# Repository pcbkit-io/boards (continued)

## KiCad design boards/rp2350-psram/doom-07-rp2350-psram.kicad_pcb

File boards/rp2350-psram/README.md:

# 07 · rp2350-psram — the bare RP2350A with QSPI flash and PSRAM on one bus

The reference device's chip without the module: an RP2350A with Raspberry Pi's minimal design
(core switching regulator, 12 MHz crystal), a 16 MB W25Q128 on QSPI chip select 0 and an 8 MB
APS6404L PSRAM on the QMI's chip select 1 (GPIO8) sharing the same SCLK and SD0–SD3, so both are
memory-mapped through the XIP cache and Doom runs as an ordinary program. Two 18650 Li-ion cells
power it, behind reverse-cell and DW01A protection, charged from the USB-C by a BQ24075 with power
path, with a MAX17048 fuel gauge and a switched LDO. JLCPCB assembles everything but the display
module, which plugs into the socket it solders.

| | |
|---|---|
| Processor | RP2350A (QFN-60): 2 × **Cortex-M33** (ARMv8-M Mainline, FPU, DSP, TrustZone) **or** 2 × **Hazard3** RISC-V (RV32IMAC + Zba/Zbb/Zbs/Zbkb/Zcb/Zcmp), the architecture chosen by the image; 150 MHz; 520 KB SRAM; on-chip 1.1 V switching regulator (3.3 µH) |
| Memory | W25Q128JVSIQ 16 MB on QSPI_SS (CS0); APS6404L-3SQR 8 MB PSRAM on GPIO8 = QMI CS1 (XIP_CS1n); both mapped by the QMI (flash at 0x1000_0000, PSRAM at 0x1100_0000), 16 KB XIP cache |
| Display | 2.0" 240 × 320 IPS, ST7789 (MSP2008), SPI0 (GPIO18 SCK, GPIO19 MOSI, GPIO17 CS, GPIO16 DC, GPIO20 RES, GPIO21 backlight); landscape 320 × 240 |
| Storage | microSD on SPI1 (GPIO10–13), card detect GPIO14 |
| Input | 10 × 6 mm tact switches: GPIO0–5 (d-pad, fire, use), GPIO9, GPIO15 (strafe), GPIO25 (menu), GPIO26 (enter) |
| Sound | PIO I2S (GPIO22 BCK, GPIO23 LRCK, GPIO24 DIN) → MAX98357A → 8 Ω speaker |
| Power | 2 × 18650 Li-ion in parallel (1S2P) → reverse-cell P-FET (AO3401A) → DW01A + FS8205A; USB-C (1 A PTC + TVS) → **BQ24075** (power path SYS; USB500 mode, 800 mA charge) → TLV75533 (EN on the slide switch) → 3.3 V; **MAX17048** gauge on the pack, on I2C1 (GPIO6 SDA, GPIO7 SCL, 0x36, alert GPIO29); amplifier on SYS |
| Programming | USB-C to the RP2350's USB (27 Ω, USBLC6 ESD array): hold BOOT (1 kΩ on QSPI_SS), tap RESET → the boot ROM's UF2 drive, for ARM or RISC-V images; SWD + RUN on a 4-pin header on the back |
| Board | 144 × 110 mm, **4 layers** (In1 a solid GND plane), four M3 holes; front: display, buttons, BOOT, RESET, on/off switch, USB-C, charge LEDs, test pads; back: the RP2350 and the rest, the two 18650 holders across the top half. Net classes: 0.15 mm tracks and gaps with 0.45 / 0.2 mm vias by default (the QFN-60's 0.4 mm pitch), 0.3 mm for 3.3 V and the core, 0.6 mm with 0.8 / 0.4 mm vias for the power paths |

<!-- STATUS -->
**Board status** (measured on the dev host with PCBKit's CLI): `pcbkit check`: complete — 0 errors, 3 warnings (diff-pair-uncoupled, skew, track-width-class), 0 unrouted nets; `issues` has 3 of 3. 100 components, 75 nets, 1224 track segments (3267 mm), 166 vias.
`analysis.run { lens: "ready" }`: Typical scenario, partly by family estimates. Nothing to fix, 5 to consider, 14 ok: weigh the warnings (tell the person about the ones that are their choice), then the board is ready to order.
`pcbkit export --format fab` succeeds without `--force`: every assembled line of the BOM has an LCSC code.

| Warning | Why it stays |
|---|---|
| `diff-pair-uncoupled`, `skew` (DP / DN, ~60 mm) | USB full speed (12 Mbit/s): the connector is on the front edge, the RP2350 on the back; tens of mm uncoupled and ten of skew (~70 ps) are harmless against 4–20 ns edges |
| `track-width-class` (DP necked to 0.15 mm) | a short neck at the 0.4 mm pitch pads; a signal |
| ready lens: J3 is not on an edge | the SWD header is for a debug probe's jumper wires, not a cable to the outside |
| ready lens: thermal parameters, typical scenario | estimates of the analysis, not faults of the board |
<!-- /STATUS -->

## Run it in the browser

Open https://app.pcbkit.io/github/pcbkit-io/doom-handheld/tree/main/boards/rp2350-psram, open the
Laboratory and press **Run**: the page builds `doom/` for the RP2350 (with `DOOM1.WAD` linked into
flash), boots the image on a register-level model of the chip and its PSRAM, and draws the
display's frames on the board. Play with the keyboard (arrows, F fire, Space use, comma/period
strafe, M menu, Enter) or a gamepad (`input.js` maps a standard controller).

## Why it runs Doom

This is the reference device's software on its own board: Doom with its zone heap and screens in
the PSRAM, the shareware WAD linked into the flash, on one Hazard3 core at 150 MHz; each 320 × 200
frame goes to the display as RGB565 over SPI0 at 25 MHz. Not measured on hardware: the simulation
runs one instruction per clock and charges no flash or PSRAM latency.

## Power

Two 18650 Li-ion cells in Keystone 1042 holders on the back, in parallel (1S2P, 3.0–4.2 V, about
5–7 Ah together), as on `rp2350-handheld`:

- **Reverse cells:** an AO3401A P-MOSFET in the plus line, its gate at the cells' minus: cells put
  in backwards leave it off and the board unpowered (it conducts both ways when they are right, so
  charging goes through it too). It cannot help one cell reversed against the other: in parallel
  they would short each other, so check both against the silkscreen's + before closing a case.
- **Protection:** DW01A + FS8205A in the pack's minus: over-charge 4.3 V, over-discharge 2.4 V,
  over-current about 3 A and short circuit, for the pack. Flat-top unprotected 18650 cells fit
  the holders.
- **Charger with power path:** a TI BQ24075 (the BQ24074's sibling with SYSOFF and a fixed
  current-based termination) from the USB-C VBUS (through a 1 A PTC fuse, a 5 V TVS after it), in
  USB500 mode (at most 500 mA from the port; 5.1 kΩ on CC), 800 mA fast charge (RISET 1.13 kΩ),
  input limit RILIM 1.18 kΩ, safety timers off (two cells charge longer than its longest timer),
  TS tied to 10 kΩ (no thermistor). Its output SYS runs the board from USB when one is plugged in
  (flat or missing cells included) and from the cells otherwise.
- **Fuel gauge:** the MAX17048 measures the pack after the protection (its ModelGauge needs no
  sense resistor; two cells in parallel read as one cell of twice the capacity).
- **Rails:** SYS feeds the TLV75533 LDO (3.3 V; it follows the cells below about 3.55 V) and the
  MAX98357A directly; the slide switch on the left edge enables the LDO (100 kΩ holds it off), the
  amplifier is shut down by its SD_MODE while the RP2350 is off. The cells keep charging with the
  switch off.

| State | Current (estimate) |
|---|---|
| RP2350 at 150 MHz + PSRAM + flash | ~45 mA at 3.3 V |
| ST7789 2.0" with backlight | ~40 mA |
| MAX98357A | 20–200 mA from SYS |
| **Typical** | **~120 mA at 3.7 V** |

Two 3000 mAh cells → **about 50 h** of play (estimate). A full charge of two empty cells at 800 mA
takes about 8 h (longer from a 500 mA USB 2.0 port).

## Charging

Plug a USB-C charger or computer into the USB-C on the bottom edge. The red LED (CHG) is on while
the cells charge and goes out when they are full; the green LED (USB) is on while USB power is
present. The board runs from USB while it charges, switched on or off. Insert both cells with +
at the end the back's silkscreen marks.

## Flashing on arrival

Nothing to solder and no programmer: the RP2350's boot ROM has a USB loader.

1. Connect the USB-C to a computer.
2. Hold **BOOT**, tap **RESET**, release BOOT (or hold BOOT while plugging in): the board appears
   as the **RP2350** drive.
3. Copy `U1.uf2` onto it (the boot ROM runs Arm or RISC-V images); or
   `picotool load -x U1.uf2` with the board in BOOTSEL.

Or over SWD: the 4-pin header on the back (SWCLK, GND, SWDIO, RUN) takes a Raspberry Pi Debug
Probe. The game data goes in the flash with the program.

## Modules plugged in by hand

- **DS1: 2.0" 240 × 320 ST7789 IPS SPI module** (MSP2008 pinout, 8 pins: GND, VCC, SCL, SDA, RES,
  DC, CS, BLK) into the 1x8 socket JLCPCB solders on the front.
- An **8 Ω speaker** (up to 3 W) with a JST PH 2-pin plug into J5 at the right edge of the back.
- Two **18650 cells**.

## Firmware: build

- `doom/` is the program: `doom_rp2350.c` is the platform layer (clocks from the 12 MHz crystal,
  the PSRAM on QMI chip select 1 = GPIO8, which the firmware sets up — the boot ROM only sets up
  CS0 — the display, the buttons, the timer), the engine is sysprog21/doom_riscv, unchanged. Pins:
  display SCK GPIO18, MOSI GPIO19, CS GPIO17, D/C GPIO16, RESET GPIO20, backlight GPIO21; buttons
  up GPIO0, down 1, left 2, right 3, fire 4, use 5, strafe left 9, strafe right 15, menu 25,
  enter 26. The ST7789's IPS panel needs inversion on (INVON) for true colours. Not used yet: the
  microSD card, the amplifier, the fuel gauge; no console (GPIO0 and GPIO1 are buttons).
- **Build:** in PCBKit, the Laboratory's **Run** builds it (RISC-V, `DOOM1.WAD` linked into flash);
  then export the firmware (`export.run { format: "firmware" }`, or the app's export menu): `U1.uf2`.

## Bill of materials

Rough cost at 10 pieces (estimates): RP2350A $1.10 · W25Q128 $1.00 · APS6404L $1.20 · crystal $0.15 ·
3.3 µH inductor $0.20 · ST7789 2.0" $4.00 · microSD socket $0.60 · MAX98357A $0.90 · BQ24075 $1.10 ·
DW01A + FS8205A + AO3401A $0.25 · MAX17048 $1.60 · TLV75533 $0.20 · USB-C + ESD + TVS + PTC $0.50 ·
buttons $3.50 · passives $2.00 · two 18650 holders $9.80 · 4-layer PCB $4.00 · speaker $1.00 →
**about $37** without the cells, plus assembly.

<!-- BOM -->
The assembly BOM as `pcbkit export --format fab` writes it (JLCPCB assembly: LCSC codes; the modules' lines are their sockets):

| Qty | Refs | Part | LCSC | Footprint |
|---|---|---|---|---|
| 2 | BT1, BT2 | 1042 | C5249310 | BatteryHolder_Keystone_1042_1x18650 |
| 1 | C1 | 10uF | C19702 | C_0603_1608Metric |
| 2 | C2, C3 | 15pF | C1548 | C_0402_1005Metric |
| 16 | C4, C5, C6, C7, C8, C9, C10, C11, C12, C13, C14, C18, C19, C21, C23, C27 | 100nF | C1525 | C_0402_1005Metric |
| 5 | C15, C16, C17, cBat, cSys | 4.7uF | C1779 | C_0805_2012Metric |
| 1 | C20 | 1uF | C52923 | C_0402_1005Metric |
| 1 | C22 | 10uF | C15850 | C_0805_2012Metric |
| 3 | C28, C29, cIn | 1uF | C15849 | C_0603_1608Metric |
| 1 | D1 | tvs 5V | C918844 | D_SOD-323 |
| 1 | DS1 | Female header 1x8 2.54 mm | C2905417 | TFT_2.0in_ST7789_Socket_1x08_P2.54mm |
| 1 | F1 | PTC 1000mA | C20800 | Fuse_1206_3216Metric |
| 1 | J1 | USB_C_Receptacle_USB2.0_16P | C165948 | USB_C_Receptacle_USB2.0_16P |
| 1 | J3 | PinHeader_1x04_P2.54mm_Vertical | C2691448 | PinHeader_1x04_P2.54mm_Vertical |
| 1 | J4 | DM3AT-SF-PEJM5 | C114218 | Hirose_DM3AT_microSD_socket_push-push |
| 1 | J5 | S2B-PH-K-S(LF)(SN) | C173752 | JST_PH_S2B-PH-K_1x02_P2.00mm_Horizontal |
| 1 | L1 | 3.3uH | C83456 | L_Power_6x6mm |
| 1 | Q1 | AO3401A | C15127 | SOT-23 |
| 1 | Q2 | FS8205A | C5148694 | TSSOP-8_4.4x2.93mm_P0.65mm |
| 7 | R1, R2, R3, R4, R5, R12, rTs | 10kohm | C25744 | R_0402_1005Metric |
| 2 | R6, R16 | 100kohm | C25741 | R_0402_1005Metric |
| 3 | R7, R11, R18 | 1kohm | C11702 | R_0402_1005Metric |
| 1 | R8 | 33ohm | C25105 | R_0402_1005Metric |
| 2 | R9, R10 | 27ohm | C25100 | R_0402_1005Metric |
| 1 | R13 | 634kohm | C270588 | R_0402_1005Metric |
| 2 | R14, R15 | 5.1kohm | C25905 | R_0402_1005Metric |
| 1 | R17 | 100ohm | C25076 | R_0402_1005Metric |
| 2 | R21, R22 | 3.3kohm | C25890 | R_0402_1005Metric |
| 12 | SW1, SW2, SW3, SW4, SW5, SW6, SW7, SW8, SW9, SW10, SW11, reset | PTS645SM43SMTR92 LFS | C221880 | SW_Tactile_SPST_6x6mm_SMD |
| 1 | SW12 | MSK12C02 | C431540 | SW_Slide_SPDT_Shouhan_MSK12C02 |
| 1 | U1 | RP2350A | C42411118 | QFN-60-1EP_7x7mm_P0.4mm_EP3.4x3.4mm |
| 1 | U2 | W25Q128JVSIQ | C97521 | SOIC-8_5.23x5.28mm_P1.27mm |
| 1 | U3 | APS6404L-3SQR-SN | C5333729 | SOIC-8_3.9x4.9mm_P1.27mm |
| 1 | U4 | TLV75533PDBVR | C404027 | SOT-23-5 |
| 1 | U5 | MAX98357AETE+T | C910544 | QFN-16-1EP_3x3mm_P0.5mm_EP1.1x1.1mm |
| 1 | U6 | BQ24075RGTR | C15464 | QFN-16-1EP_3x3mm_P0.5mm_EP1.68x1.68mm |
| 1 | U7 | MAX17048G+T10 | C2682616 | DFN-8-1EP_2x2mm_P0.5mm_EP0.8x1.2mm |
| 1 | U8 | DW01A | C351410 | SOT-6_1.6x2.9mm_P0.95mm |
| 1 | U9 | ESD 2-line | C7519 | SOT-23-6 |
| 1 | Y1 | 12MHz 10pF | C20625731 | Crystal_SMD_3225-4Pin |
| 1 | ledChg | red | C2286 | LED_0603_1608Metric |
| 1 | ledPg | green | C12624 | LED_0603_1608Metric |
| 2 | rChg, rPg | 1.5kohm | C25867 | R_0402_1005Metric |
| 1 | rIlim | 1.18kohm | C270651 | R_0402_1005Metric |
| 1 | rIset | 1.13kohm | C67014 | R_0402_1005Metric |
<!-- /BOM -->

## What PCBKit's engine must model to simulate it faithfully

The RP2350 SoC being written now (Hazard3, Xh3irq, TIMER, IO_BANK0, SIO, RESETS), plus: the **QMI
with both chip selects** — CS0 set up by the boot ROM, **CS1 configured by the firmware** (M1 timing
and read/write formats, GPIO8 funcsel XIP_CS1n) — in front of **two board memory components** on one
shared QSPI bus (W25Q128, APS6404L); the XIP cache including writes to PSRAM; the boot ROM's
IMAGE_DEF search and BOOTSEL entry by QSPI_SS low; PL022 SPI0/SPI1 with DMA; PIO for I2S; I2C1
(DesignWare) to the MAX17048 model; the core regulator as a fixed 1.1 V; and the board's BQ24075 /
two-cell / protection / LDO chain.

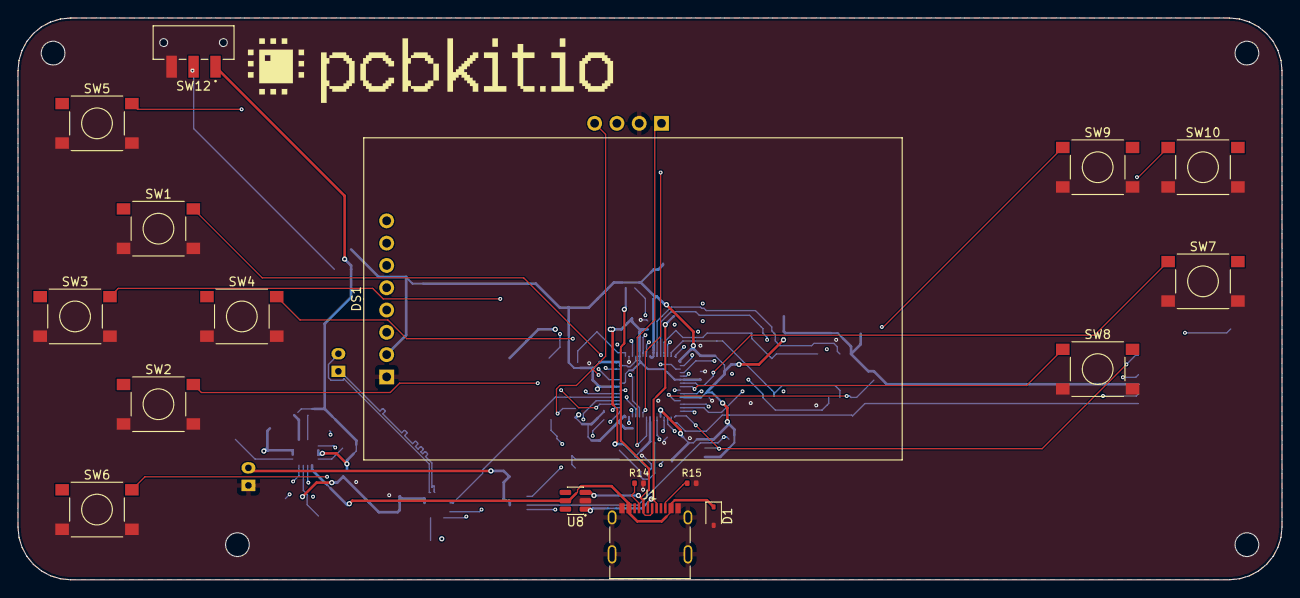
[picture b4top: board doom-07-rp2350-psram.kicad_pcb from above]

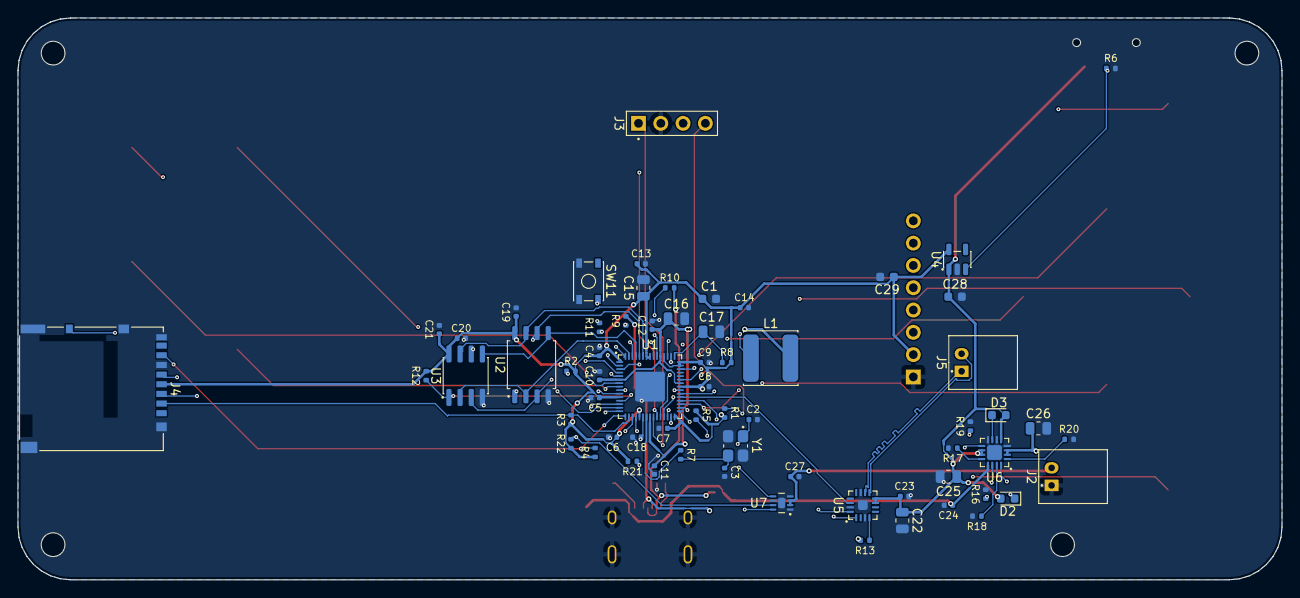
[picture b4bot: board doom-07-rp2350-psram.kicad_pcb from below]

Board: 4 copper layers, 144.0 x 64.0 mm, 87 parts (65 on the bottom side), 66 nets.

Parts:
C1: 10uF; C_0603_1608Metric
C2, C3, C18: 15pF; C_0402_1005Metric
C4, C5, C6, C7, C8, C9, C10, C11, C12, C13, C14, C19, C21, C23, C27: 100nF; C_0402_1005Metric
C15, C16, C17, C25, C26: 4.7uF; C_0805_2012Metric
C20, C24: 1uF; C_0402_1005Metric
C22: 10uF; C_0805_2012Metric
C28, C29: 1uF; C_0603_1608Metric
D1: tvs 5V; D_SOD-323
D2: red; LED_0603_1608Metric
D3: green; LED_0603_1608Metric
DS1: MSP2008 2.0in 240x320 IPS SPI module (ST7789); TFT_2.0in_ST7789_Socket_1x08_P2.54mm
H1, H2, H3, H4: MountingHole_2.7mm_M2.5
J1: USB_C_Receptacle_USB2.0_16P
J2, J5: S2B-PH-K-S(LF)(SN); JST_PH_S2B-PH-K_1x02_P2.00mm_Horizontal
J3: PinHeader_1x04_P2.54mm_Vertical
J4: DM3AT-SF-PEJM5; Hirose_DM3AT_microSD_socket_push-push
L1: 3.3uH; L_Power_6x6mm
R1, R2, R3, R4, R5, R12, R20: 10kohm; R_0402_1005Metric
R6: 100kohm; R_0402_1005Metric
R7, R11: 1kohm; R_0402_1005Metric
R8: 33ohm; R_0402_1005Metric
R9, R10: 27ohm; R_0402_1005Metric
R13: 634kohm; R_0402_1005Metric
R14, R15: 5.1kohm; R_0402_1005Metric
R16: 1.13kohm; R_0402_1005Metric
R17: 1.18kohm; R_0402_1005Metric
R18: 4.12kohm; R_0402_1005Metric
R19: 46.4kohm; R_0402_1005Metric
R21, R22: 3.3kohm; R_0402_1005Metric
SW1, SW2, SW3, SW4, SW5, SW6, SW7, SW8, SW9, SW10: PTS645SM43SMTR92 LFS; SW_Tactile_SPST_6x6mm_SMD
SW11: PTS810 SJM 250 SMTR LFS; SW_Tactile_SPST_4.2x3.2mm_SMD
SW12: JS102011SAQN; SW_Slide_SPDT_CK_JS102011SAQN_Horizontal
U1: RP2350A; QFN-60-1EP_7x7mm_P0.4mm_EP3.4x3.4mm
U2: W25Q128JVSIQ; SOIC-8_5.23x5.28mm_P1.27mm
U3: APS6404L-3SQR-SN; SOIC-8_3.9x4.9mm_P1.27mm
U4: TLV75533PDBVR; SOT-23-5
U5: MAX98357AETE+T; QFN-16-1EP_3x3mm_P0.5mm_EP1.1x1.1mm
U6: BQ24074RGTR; QFN-16-1EP_3x3mm_P0.5mm_EP1.68x1.68mm
U7: MAX17048G+T10; DFN-8-1EP_2x2mm_P0.5mm_EP0.8x1.2mm
U8: ESD 2-line; SOT-23-6
Y1: 12MHz 10pF; Crystal_SMD_3225-4Pin
logo: Logo_PCBKit_pcbkit.io

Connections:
BOOTSEL: R11.2, SW11.1, SW11.2
DN: J1.A7, J1.B7, R10.2, U8.3
DOWN: SW2.1, SW2.2, U1.3
DP: J1.A6, J1.B6, R9.2, U8.1
ENTER: SW10.1, SW10.2, U1.40
FIRE: SW7.1, SW7.2, U1.7
FUEL_ALRT: R5.2, U1.43, U7.5
GND: C1.2, C2.2, C3.2, C4.2, C5.2, C6.2, C7.2, C8.2, C9.2, C10.2, C11.2, C12.2, C13.2, C14.2, C15.2, C16.2, C17.2, C18.2, C19.2, C20.2, C21.2, C22.2, C23.2, C24.2, C25.2, C26.2, C27.2, C28.2, C29.2, D1.2, DS1.1, J1.A1, J1.B1, J1.S1, J2.1, J3.2, J4.6, J4.10, J4.SH, R6.2, R14.2, R15.2, R16.2, R17.2, R18.2, R19.2, R20.2, SW1.3, SW1.4, SW2.3, SW2.4, SW3.3, SW3.4, SW4.3, SW4.4, SW5.3, SW5.4, SW6.3, SW6.4, SW7.3, SW7.4, SW8.3, SW8.4, SW9.3, SW9.4, SW10.3, SW10.4, SW11.3, SW11.4, SW12.3, U1.47, U1.61, U2.4, U3.4, U4.2, U5.3, U5.11, U5.15, U5.17, U6.4, U6.6, U6.8, U6.17, U7.1, U7.4, U7.6, U7.9, U8.2, Y1.2, Y1.4
I2S_BCK: U1.34, U5.16
I2S_DIN: U1.36, U5.1
I2S_LRCK: U1.35, U5.14
LCD_BL: DS1.8, U1.33
LCD_CS: DS1.7, U1.28
LCD_DC: DS1.6, U1.27
LCD_RST: DS1.5, U1.32
LDO_EN: R6.1, SW12.2, U4.3
LEFT: SW3.1, SW3.2, U1.4
MENU: SW9.1, SW9.2, U1.37
MOSI: DS1.4, U1.31
unnamed: C2.1, C18.1, U1.21, Y1.1
unnamed: C17.1, R8.1, U1.46
unnamed: D2.1, U6.9
unnamed: D3.1, U6.7
unnamed: L1.1, U1.48
unnamed: R7.1, U1.22
unnamed: R9.1, U1.52
unnamed: R10.1, U1.51
unnamed: R13.1, U5.4
unnamed: R16.1, U6.16
unnamed: R17.1, U6.12
unnamed: R18.1, U6.15
unnamed: R19.1, U6.14
unnamed: R20.1, U6.1
PSRAM_CS: R12.1, U1.12, U3.1
QSPI_SCLK: U1.56, U2.6, U3.6
QSPI_SD0: U1.57, U2.5, U3.5
QSPI_SD1: U1.59, U2.2, U3.2
QSPI_SD2: U1.58, U2.3, U3.3
QSPI_SD3: U1.55, U2.7, U3.7
QSPI_SS: R11.1, U1.60, U2.1
RIGHT: SW4.1, SW4.2, U1.5
RUN: J3.4, R1.1, U1.26
SCK: DS1.3, U1.29
SCL: R22.2, U1.10, U7.7
SDA: R21.1, U1.9, U7.8
SD_CD: J4.9, R2.1, U1.18
SD_CS: J4.2, R3.2, U1.17
SD_MISO: J4.7, R4.2, U1.16
SD_MOSI: J4.3, U1.15
SD_SCK: J4.5, U1.14
SPK_N: J5.1, U5.10
SPK_P: J5.2, U5.9
STRAFE_L: SW5.1, SW5.2, U1.13
STRAFE_R: SW6.1, SW6.2, U1.19
SWCLK: J3.1, U1.24
SWDIO: J3.3, U1.25
U1Support/XO: C3.1, R7.2, Y1.3
UP: SW1.1, SW1.2, U1.2
USE: SW8.1, SW8.2, U1.8
V1V1: C10.1, C11.1, C12.1, C16.1, L1.2, U1.6, U1.23, U1.39, U1.50
V3: C1.1, C4.1, C5.1, C6.1, C7.1, C8.1, C9.1, C13.1, C14.1, C15.1, C19.1, C20.1, C21.1, C29.1, DS1.2, J4.4, R1.2, R2.2, R3.1, R4.1, R5.1, R8.2, R12.2, R13.2, R21.2, R22.1, U1.1, U1.11, U1.20, U1.30, U1.38, U1.44, U1.45, U1.49, U1.53, U1.54, U2.8, U3.8, U4.5
VBAT: C26.1, C27.1, J2.2, U6.2, U6.3, U7.2, U7.3
VBUS: C24.1, D1.1, J1.A4, J1.B4, U6.13, U8.5
VSYS: C22.1, C23.1, C25.1, C28.1, D2.2, D3.2, SW12.1, U4.1, U5.7, U5.8, U6.5, U6.10, U6.11
usb/power/cc1: J1.A5, R14.1
usb/power/cc2: J1.B5, R15.1

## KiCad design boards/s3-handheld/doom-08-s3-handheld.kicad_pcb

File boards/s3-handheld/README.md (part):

# 08 · s3-handheld — Xtensa LX7 with 8 MB of PSRAM, the classic ESP32 Doom

The best-trodden path to a Doom handheld: an ESP32-S3-WROOM-1-N16R8 module (16 MB flash and 8 MB
octal PSRAM inside), the 2.8" ILI9341 touch TFT, a microSD slot on SDMMC, ten buttons, an I2S
amplifier, and two 18650 cells with protection, a power-path charger from USB-C and a fuel gauge.
JLCPCB assembles everything but the display module, which plugs into the socket it solders.

| | |
|---|---|
| Processor | ESP32-S3-WROOM-1-N16R8: ESP32-S3, 2 × **Xtensa LX7** (windowed registers, 128-bit SIMD "PIE" extension, single-precision FPU) at 240 MHz, 512 KB SRAM, 16 MB quad flash, 8 MB **octal** PSRAM (OPI, 80 MHz DDR, behind the cache and MMU) |
| Display | 2.8" 240 × 320 ILI9341 + XPT2046 touch on SPI2 at 40 MHz (IO12 SCK, IO11 MOSI, IO13 MISO, IO10 CS, IO9 DC, IO14 RESET, IO21 backlight; touch CS IO47, IRQ IO48) |
| Storage | microSD on SDMMC host, 1-bit mode (IO39 CLK, IO38 CMD, IO40 D0; D1–D3 pulled up) |
| Input | 10 × 6 mm tact switches: up IO15, down IO16, left IO17, right IO7, fire IO2, use IO41, strafe IO42 / IO1, MENU IO0 (= BOOT), enter RXD0; RESET (EN) beside them |
| Sound | I2S0 (IO4 BCLK, IO5 LRCLK, IO6 DIN) → MAX98357A (mono mix) → 8 Ω speaker on J5 (bottom edge); amplifier on SYS |
| Power | 2 × 18650 Li-ion in parallel (1S2P) in Keystone 1042 holders → reverse-cell P-FET (AO3401A) → DW01A + FS8205A; USB-C → **BQ24075** (power path, USB500, 800 mA charge) → SYS → TLV75533 (EN on the slide switch) → 3.3 V; **MAX17048** fuel gauge on the pack, I2C (IO8 SDA, IO18 SCL, 0x36) |
| Programming | USB-C to the S3's USB (IO19/IO20): USB Serial/JTAG, `esptool`, or TinyUSB; RESET and BOOT (= MENU) on the front |
| Board | 156 × 110 mm, **4 layers**, four M3 holes; front: display, buttons, RESET, on/off switch, charger and its LEDs, test pads, speaker connector; back: module (top edge, antenna 6 mm past it), USB-C (top edge, beside the module), microSD (bottom edge), amplifier, regulator, fuel gauge, the two cells |

<!-- STATUS -->
**Board status** (measured on the dev host with PCBKit's CLI): `pcbkit check`: complete — 0 errors, 2 warnings (diff-pair-uncoupled, skew), 0 unrouted nets; `issues` has 2 of 2. 75 components, 60 nets, 824 track segments (3158 mm), 85 vias.
`analysis.run { lens: "ready" }`: Typical scenario, partly by family estimates. Nothing to fix, 3 to consider, 15 ok: weigh the warnings (tell the person about the ones that are their choice), then the board is ready to order.
`pcbkit export --format fab` succeeds without `--force`: every assembled line of the BOM has an LCSC code.
<!-- /STATUS -->

Warnings left, and why they are acceptable:

| Warning | Why |
|---|---|
| `diff-pair-uncoupled`, `skew` on DP / DN | USB full speed (12 Mbit/s): the pair runs from the connector beside the module around it to the module's USB pins, partly apart; tens of mm uncoupled and of skew are tenths of a nanosecond against 4–20 ns edges |
| heat sources need exact thermal parameters; chips estimated by their family | the thermal estimate's own caveat: nothing on this board dissipates more than a few hundred mW |

## Run it in the browser

Open https://app.pcbkit.io/github/pcbkit-io/doom-handheld/tree/main/boards/s3-handheld, open the
Laboratory and press **Build & run**: the page builds `doom/` for the ESP32-S3's Xtensa LX7 with
Espressif's LLVM (with `DOOM1.WAD` linked into its flash), boots it the way the chip's boot ROM
boots an image from flash, and draws the ILI9341's frames on the board. Play with the keyboard
(arrows, F fire, Space use, comma/period strafe, M menu, Enter) or a gamepad (`input.js`).

## Why it runs Doom

The program runs in place from the module's flash through the instruction cache, and the game's
data, the shareware WAD, is linked into the same flash and read in place through the data cache:
no SD card or partition table is needed. The start-up (PCBKit's ESP32-S3 kit) stops the boot ROM's
watchdogs, moves the CPU to the PLL at 160 MHz, maps the program's flash pages and brings the octal
PSRAM up as ESP-IDF does (20 MHz, no timing tuning), which holds the zone heap (5 MB), the four
screens and the visplanes; internal SRAM keeps the engine's other state and the stack. The board's
copy of the engine keeps its trigonometric tables in flash and puts two large arrays in the PSRAM
(`doom/doom_esp32s3.c` says where). Each frame goes through Doom's palette to RGB565 and to the
ILI9341's middle 320 × 200 (landscape) on GP-SPI2 at 40 MHz, 64 bytes a transaction: about 26 ms of
the bus a frame, so the display, not the CPU, caps it near 25 fps. Measured in PCBKit's simulator:
the title by 4 s of device time, the demo by 9 s; the simulator runs it faster than real time.

## Power

Two 18650 Li-ion cells in Keystone 1042 holders on the back, in parallel (1S2P, 3.0–4.2 V). From the
cells to the board:

- **Reverse cells:** an AO3401A P-MOSFET in the plus line, its gate at the cells' minus: cells put
  in backwards leave it off and the board unpowered (it conducts both ways when they are right, so
  charging goes through it too). It cannot help one cell reversed against the other: in parallel
  they would short each other, so check both against the silkscreen's + before closing a case.
- **Protection:** DW01A + FS8205A in the pack's minus: over-charge 4.3 V, over-discharge 2.4 V,
  over-current about 3 A and short circuit, for the pack.
- **Charger with power path:** a TI BQ24075 (the BQ24074's sibling with SYSOFF and a fixed
  termination, as on boards/rp2350-handheld) from the USB-C's VBUS (5.1 kΩ CC pull-downs), in
  USB500 mode (at most 500 mA from the port), 800 mA fast charge (RISET 1.13 kΩ), input limit by
  RILIM 1.18 kΩ, safety timers off (two cells charge longer than its longest timer; termination is
  by current), TS tied to 10 kΩ (no thermistor). Its output SYS runs the board from USB when one is
  plugged in and from the cells otherwise.
- **Rails:** SYS feeds the TLV75533 LDO (3.3 V, 500 mA: the module, the display, the card) and the
  MAX98357A directly. Near empty (3.0–3.3 V cells) the LDO drops out and 3.3 V follows the cells;
  the S3 runs to 3.0 V, and the fuel gauge tells the firmware when to stop.
- **Fuel gauge:** the MAX17048 measures the pack after the reverse-cell FET (ModelGauge, no sense
  resistor) and reports its state of charge on I2C.
- **On/off:** the slide switch on the left edge drives the LDO's enable (off: the 3.3 V rail is off,
  the amplifier shut down by its SD_MODE pull-up; the charger still charges).

| State | Current (estimate) |
|---|---|
| ESP32-S3, two cores at 240 MHz, radio off | 60–90 mA |
| PSRAM active | ~15 mA |
| ILI9341 with backlight | 60–80 mA |
| MAX98357A | 20–200 mA from SYS |
| **Typical** | **~200 mA at 3.7 V** |

Two 3000 mAh cells → **~25 h**; with Wi-Fi on (peaks 350 mA) less. A full charge of two empty cells
at 800 mA takes about 8 h.

## Charging

Plug any USB-C charger or computer into the USB-C on the back's top edge. The red LED (CHG) is on
while the cells charge and goes out when they are full; the green LED (USB) is on while USB power
is present. The board runs from USB while it charges, switched on or off. Insert the cells with +
at the end the back's silkscreen marks.

## Modules plugged in by hand

The assembly solders a 1x14 female socket; the module is bought separately and plugged in:

- **DS1: 2.8" 240 × 320 ILI9341 SPI TFT with XPT2046 touch** (MSP2807, 14 pins: VCC, GND, CS,
  RESET, DC, SDI, SCK, LED, SDO, T_CLK, T_CS, T_DIN, T_DO, T_IRQ), on the front.
- An 8 Ω speaker (1–3 W) on the JST PH 2-pin connector J5 at the bottom edge; a microSD card in J4.

The ESP32-S3-WROOM-1-N16R8 itself is soldered by the assembly (LCSC C2913202).

## Firmware: build and flash

- **Build:** in PCBKit, the Laboratory's **Build & run** builds `doom/` (Xtensa LX7, Espressif's
  LLVM, the kit's start-up and link layout); then export the firmware
  (`export.run { format: "firmware" }`): `U1.bin`, the whole flash from offset 0 (the boot image the
  ROM loads, then the program's code and constants and the WAD at their pages). No 2nd-stage
  bootloader or partition table: the ROM boots the image directly.
- **Flashing on arrival:** switch the board on and plug its USB-C into a computer: the S3's
  USB Serial/JTAG enumerates (303a:1001, `/dev/ttyACM0` or a COM port) even with the module's flash
  blank, and `esptool` resets the chip into its ROM download mode through it by itself:
  `esptool.py --chip esp32s3 -p /dev/ttyACM0 write_flash 0x0 U1.bin` (or the browser's ESP Web
  Flasher at offset 0). If a running program has taken the USB pins over: hold MENU (IO0), press and
  release RESET, release MENU: ROM download mode, then flash as above. Press RESET: Doom starts.

## Bill of materials

Rough cost at 10 pieces (estimates, JLCPCB prices): ESP32-S3-WROOM-1-N16R8 $4.50 · ILI9341 2.8" touch
$7.00 · microSD socket $0.90 · MAX98357A $1.00 · BQ24075 $1.10 · MAX17048 $1.20 · DW01A + FS8205A +
AO3401A $0.25 · TLV75533 $0.15 · two Keystone 1042 $9.80 · USB-C + ESD $0.40 · buttons $3.00 ·
passives $1.00 · 4-layer PCB $4.00 · speaker $1.00 → **about $35** without the cells and assembly fees.

<!-- BOM -->
The assembly BOM as `pcbkit export --format fab` writes it (JLCPCB assembly: LCSC codes; the modules' lines are their sockets):

| Qty | Refs | Part | LCSC | Footprint |
|---|---|---|---|---|
| 2 | BT1, BT2 | 1042 | C5249310 | BatteryHolder_Keystone_1042_1x18650 |
| 1 | C1 | 10uF | C19702 | C_0603_1608Metric |
| 1 | C2 | 22uF | C29277 | C_0805_2012Metric |
| 1 | C3 | 22uF | C5672 | C_1206_3216Metric |
| 4 | C4, C7, C8, C11 | 100nF | C1525 | C_0402_1005Metric |
| 1 | C5 | 1uF | C52923 | C_0402_1005Metric |
| 1 | C6 | 10uF | C15850 | C_0805_2012Metric |
| 3 | C12, C13, cIn | 1uF | C15849 | C_0603_1608Metric |
| 1 | D1 | tvs 5V | C502527 | D_SOD-323 |
| 1 | DS1 | Female header 1x14 2.54 mm | C2905420 | TFT_2.8in_ILI9341_Socket_1x14_P2.54mm |
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
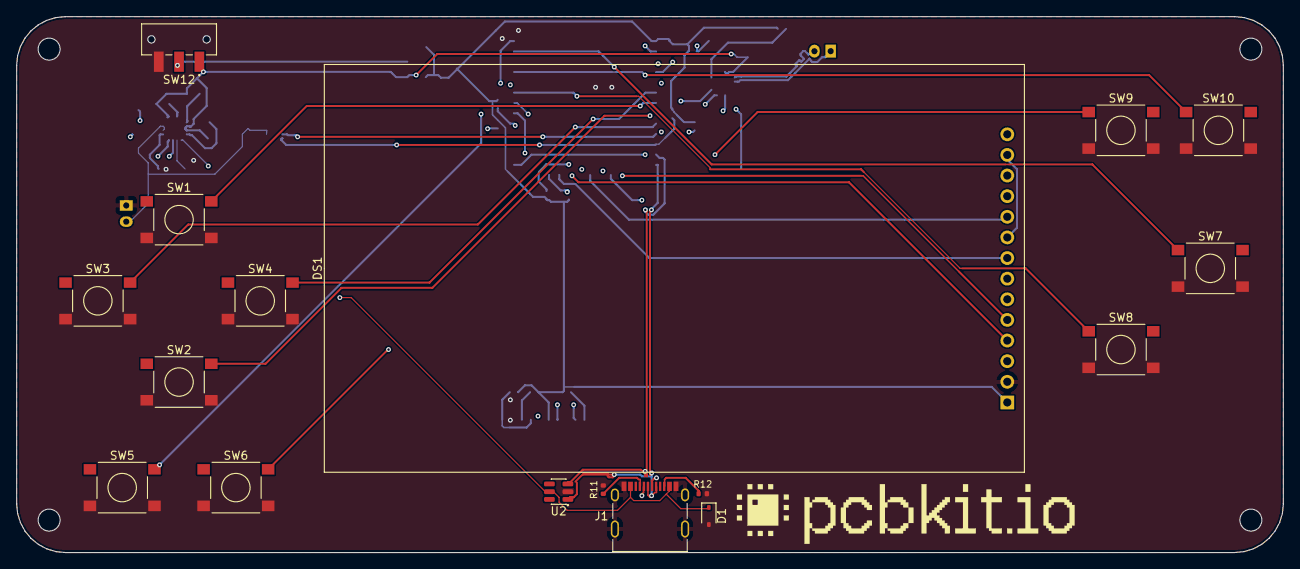
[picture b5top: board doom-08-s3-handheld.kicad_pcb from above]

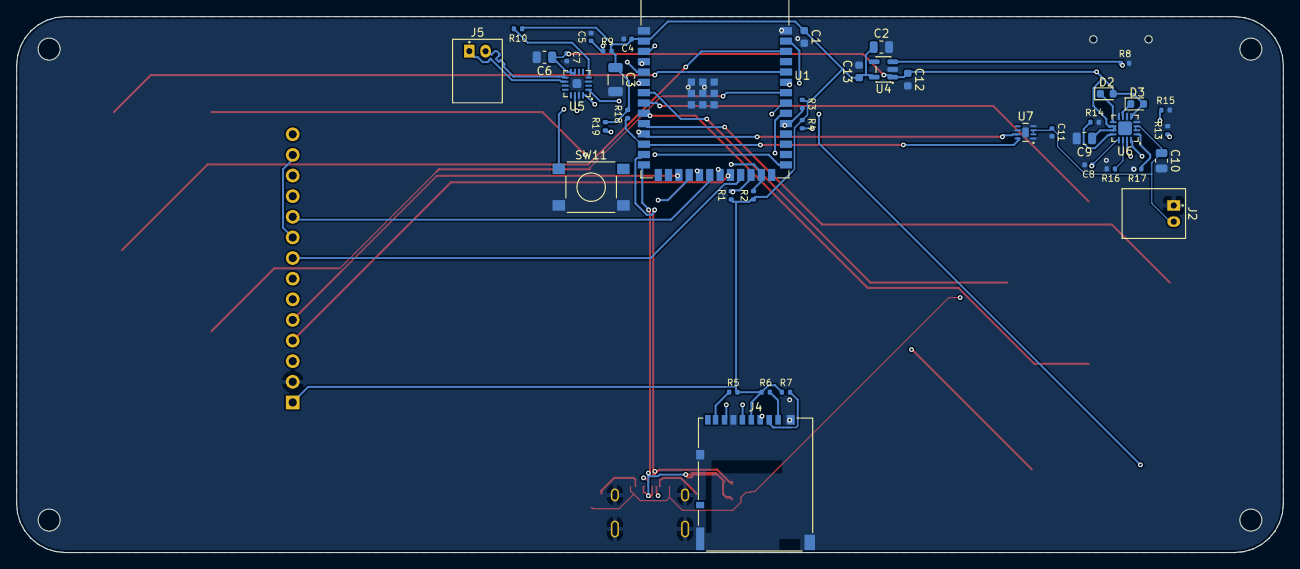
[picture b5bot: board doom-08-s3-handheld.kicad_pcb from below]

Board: 4 copper layers, 156.0 x 66.0 mm, 63 parts (41 on the bottom side), 51 nets.

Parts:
C1: 10uF; C_0603_1608Metric
C2: 22uF; C_0805_2012Metric
C3: 22uF; C_1206_3216Metric
C4, C7, C11: 100nF; C_0402_1005Metric
C5, C8: 1uF; C_0402_1005Metric
C6: 10uF; C_0805_2012Metric
C9, C10: 4.7uF; C_0805_2012Metric
C12, C13: 1uF; C_0603_1608Metric
D1: tvs 5V; D_SOD-323
D2: red; LED_0603_1608Metric
D3: green; LED_0603_1608Metric
DS1: MSP2807 2.8in 240x320 SPI TFT module with touch (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; TFT_2.8in_ILI9341_Socket_1x14_P2.54mm
H1, H2, H3, H4: MountingHole_2.7mm_M2.5
J1: USB_C_Receptacle_USB2.0_16P
J2, J5: S2B-PH-K-S(LF)(SN); JST_PH_S2B-PH-K_1x02_P2.00mm_Horizontal
J4: DM3AT-SF-PEJM5; Hirose_DM3AT_microSD_socket_push-push
R1, R2, R3, R4, R5, R6, R7, R9, R17: 10kohm; R_0402_1005Metric
R8: 100kohm; R_0402_1005Metric
R10: 634kohm; R_0402_1005Metric
R11, R12: 5.1kohm; R_0402_1005Metric
R13: 1.13kohm; R_0402_1005Metric
R14: 1.18kohm; R_0402_1005Metric
R15: 4.12kohm; R_0402_1005Metric
R16: 46.4kohm; R_0402_1005Metric
R18, R19: 3.3kohm; R_0402_1005Metric
SW1, SW2, SW3, SW4, SW5, SW6, SW7, SW8, SW9, SW10, SW11: PTS645SM43SMTR92 LFS; SW_Tactile_SPST_6x6mm_SMD
SW12: JS102011SAQN; SW_Slide_SPDT_CK_JS102011SAQN_Horizontal
U1: ESP32-S3-WROOM-1-N16R8; ESP32-S3-WROOM-1_module_18x25.5mm_40_edge_pads_EPAD
U2: ESD 2-line; SOT-23-6
U4: TLV75533PDBVR; SOT-23-5
U5: MAX98357AETE+T; QFN-16-1EP_3x3mm_P0.5mm_EP1.1x1.1mm
U6: BQ24074RGTR; QFN-16-1EP_3x3mm_P0.5mm_EP1.68x1.68mm
U7: MAX17048G+T10; DFN-8-1EP_2x2mm_P0.5mm_EP0.8x1.2mm
logo: Logo_PCBKit_pcbkit.io

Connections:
DN: J1.A7, J1.B7, U1.13, U2.3
DOWN: SW2.1, SW2.2, U1.9
DP: J1.A6, J1.B6, U1.14, U2.1
EN: C5.1, R9.1, SW11.1, SW11.2, U1.3
ENTER: SW10.1, SW10.2, U1.36
FIRE: SW7.1, SW7.2, U1.38
GND: C1.2, C2.2, C3.2, C4.2, C5.2, C6.2, C7.2, C8.2, C9.2, C10.2, C11.2, C12.2, C13.2, D1.2, DS1.2, J1.A1, J1.B1, J1.S1, J2.1, J4.6, J4.SH, R8.2, R11.2, R12.2, R13.2, R14.2, R15.2, R16.2, R17.2, SW1.3, SW1.4, SW2.3, SW2.4, SW3.3, SW3.4, SW4.3, SW4.4, SW5.3, SW5.4, SW6.3, SW6.4, SW7.3, SW7.4, SW8.3, SW8.4, SW9.3, SW9.4, SW10.3, SW10.4, SW11.3, SW11.4, SW12.3, U1.1, U1.40, U1.41, U2.2, U4.2, U5.3, U5.11, U5.15, U5.17, U6.4, U6.6, U6.8, U6.17, U7.1, U7.4, U7.6, U7.9
I2S_BCK: U1.4, U5.16
I2S_DIN: U1.6, U5.1
I2S_LRCK: U1.5, U5.14
LCD_BL: DS1.8, U1.23
LCD_CS: DS1.3, U1.18
LCD_DC: DS1.5, U1.17
LCD_RST: DS1.4, U1.22
LDO_EN: R8.1, SW12.2, U4.3
LEFT: SW3.1, SW3.2, U1.10
MENU: SW9.1, SW9.2, U1.27
MISO: DS1.9, DS1.13, U1.21
MOSI: DS1.6, DS1.12, U1.19
unnamed: D2.1, U6.9
unnamed: D3.1, U6.7
unnamed: R10.2, U5.4
unnamed: R13.1, U6.16
unnamed: R14.1, U6.12
unnamed: R15.1, U6.15
unnamed: R16.1, U6.14
unnamed: R17.1, U6.1
RIGHT: SW4.1, SW4.2, U1.7
SCK: DS1.7, DS1.10, U1.20
SCL: R19.1, U1.11, U7.7
SDA: R18.1, U1.12, U7.8
SD_CLK: J4.5, U1.32
SD_CMD: J4.3, R3.2, U1.31
SD_D0: J4.7, R4.2, U1.33
SD_D1: J4.8, R5.1
SD_D2: J4.1, R6.2
SD_D3: J4.2, R7.2
SPK_N: J5.1, U5.10
SPK_P: J5.2, U5.9
STRAFE_L: SW5.1, SW5.2, U1.35
STRAFE_R: SW6.1, SW6.2, U1.39
T_CS: DS1.11, R1.2, U1.24
T_IRQ: DS1.14, R2.2, U1.25
UP: SW1.1, SW1.2, U1.8
USE: SW8.1, SW8.2, U1.34
V3: C1.1, C2.1, C3.1, C4.1, C13.1, DS1.1, J4.4, R1.1, R2.1, R3.1, R4.1, R5.2, R6.1, R7.1, R9.2, R10.1, R18.2, R19.2, U1.2, U4.5
VBAT: C10.1, C11.1, J2.2, U6.2, U6.3, U7.2, U7.3
VBUS: C8.1, D1.1, J1.A4, J1.B4, U2.5, U6.13
VSYS: C6.1, C7.1, C9.1, C12.1, D2.2, D3.2, SW12.1, U4.1, U5.7, U5.8, U6.5, U6.10, U6.11
usb/power/cc1: J1.A5, R11.1
usb/power/cc2: J1.B5, R12.1

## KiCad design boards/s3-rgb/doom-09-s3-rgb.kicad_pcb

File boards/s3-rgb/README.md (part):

# 09 · s3-rgb — a 4.3" RGB-panel Doom on the ESP32-S3's LCD_CAM

The big-screen variant: the ESP32-S3 scans a **raw RGB TFT** (no controller, no frame memory) out of
a frame buffer in its octal PSRAM with the LCD_CAM peripheral and DMA — the architecture of the
popular ESP32-S3 "4.3-inch" boards. Ten buttons on an I2C expander (the pins all go to the panel),
stereo sound through a DAC and an amplifier, and two 18650 cells it charges from its USB-C port.
JLCPCB assembles everything; the panel is taped on and plugged in by hand.

| | |
|---|---|
| Processor | ESP32-S3-WROOM-1-N16R8 (2 × Xtensa LX7 240 MHz, 512 KB SRAM, 16 MB flash, 8 MB octal PSRAM) |
| Display | Newhaven **NHD-4.3-480272EF-ASXN**: 4.3" 480 × 272, 24-bit RGB parallel, DE mode, DCLK 9–15 MHz; driven as RGB565 (R3–R7 IO1/2/4/5/6, G2–G7 IO7/15/16/17/18/8, B3–B7 IO9–IO13; PCLK IO42, DE IO40, VSYNC IO41, HSYNC IO39; the low bits grounded) through a 40-pin 0.5 mm FFC connector (Molex 54132-4062) on the back at the top edge: the panel's cable folds over the edge into it |
| Backlight | 12 white LEDs, 25.6 V at 40 mA: **MT3608 boost as a constant-current driver** from SYS (FB regulates 0.6 V over 15 Ω), EN/PWM on IO46 (a strap that must be low at reset: 100 kΩ pull-down) |
| Input | 10 tact switches on an **MCP23017** (I2C 0x20, IO14 SDA, IO38 SCL), interrupt on change to IO3 |
| Sound | I2S (IO47 BCK, IO48 LRCK, IO21 DIN) → **PCM5102A** DAC → **PAM8403** stereo class-D from SYS (SHDN on 3.3 V: asleep when switched off) → two 4–8 Ω speakers on JST PH plugs at the left and right edges |
| Power | **2 × 18650 Li-ion in parallel** (1S2P) behind a reverse-cell P-FET (AO3401A) and DW01A + FS8205A protection; USB-C (1 A PTC fuse, TVS, ESD array) → **BQ24075** charger with power path → SYS for the backlight driver and the amplifier → **TLV75533** low-dropout regulator for 3.3 V; on/off slide switch on the regulator's EN |
| Programming | USB-C D+/D− to the S3's native USB (IO19/IO20): esptool over USB-Serial/JTAG; RESET (EN) and BOOT (IO0) buttons on the back |
| Board | 182 × 80 mm, **4 layers**, four M3 holes; front: the panel on tape (outline in the silkscreen), buttons, the power corner (USB-C at the top edge, charger, CHG/USB LEDs, on/off switch); back: two 18650 holders along the bottom edge, module (antenna past the top edge), FFC connector at the top edge, protection, regulator, backlight driver, expander, audio, test pads |

<!-- STATUS -->
**Board status** (measured on the dev host with PCBKit's CLI): `pcbkit check`: complete — 0 errors, 1 warning (diff-pair-uncoupled), 0 unrouted nets; `issues` has 1 of 1. 97 components, 85 nets, 882 track segments (3572 mm), 99 vias.
`analysis.run { lens: "ready" }`: Typical scenario from the parts' datasheets. Nothing to fix, 3 to consider, 14 ok: weigh the warnings (tell the person about the ones that are their choice), then the board is ready to order.
`pcbkit export --format fab` succeeds without `--force`: every assembled line of the BOM has an LCSC code.
<!-- /STATUS -->

What `check` and the ready lens leave to weigh, and why each is acceptable:

| Warning | Why it is acceptable |
|---|---|
| `diff-pair-uncoupled`: DP / DN about 21 mm uncoupled (128 mm coupled), over the default 10 mm | USB full speed (12 Mbit/s): the connector is at the top left, the module at the top right; the uncoupled stretch is at the two ends, harmless at 4–20 ns edges |
| GND's copper heats up by 28 °C (1.5 A on the thinnest GND track) | the lens rates one 0.15 mm GND track alone; GND is also a pour on the top, inner and bottom layers that carries the return current beside it (the Current lens notes the pour runs it cooler) |
| 6 heat sources need exact thermal parameters | the regulator, charger, boost, amplifier, DAC and module dissipate well under 0.5 W each in this design; the estimate uses generic package limits, as for every board here |

## Run it in the browser

Open https://app.pcbkit.io/github/pcbkit-io/doom-handheld/tree/main/boards/s3-rgb, open the
Laboratory and press **Build & run**: the page builds `doom/` for the ESP32-S3's Xtensa LX7 with
Espressif's LLVM (with `DOOM1.WAD` linked into its flash), boots it the way the chip's boot ROM
boots an image from flash, and shows on the panel the frames LCD_CAM scans out of the PSRAM. The
buttons reach the program through the MCP23017, as on the board. Play with the keyboard (arrows,
F fire, Space use, comma/period strafe, M menu, Enter) or a gamepad (`input.js`).

## Why it runs Doom (and what the screen costs)

Doom is the same port as variant 08 (the program and the WAD in place in flash, the zone heap,
screens and visplanes in the octal PSRAM, here at 40 MHz). The difference is the display: the
LCD_CAM peripheral in RGB mode streams a 480 × 272 RGB565 frame buffer from the PSRAM by GDMA
without end, at a 10 MHz pixel clock with the Newhaven sheet's porches (HSYNC 1 + 43 + 480 + 2,
VSYNC 1 + 12 + 272 + 4): 66 Hz, 261 KB a frame, about 17 MB/s of the PSRAM's ~40 MB/s at 40 MHz
octal DDR (estimate). Each Doom frame is scaled 1.36 times through the palette into the middle
435 × 272 of that buffer and written back from the data cache (the DMA reads the PSRAM, not the
cache). The panel never stops refreshing, which is why this design matters to the simulator: the
display is a **timed bus master**, not a sequence of SPI commands. The ten buttons are read from
the MCP23017 over I2C0 (400 kHz) once a tic. Measured in PCBKit's simulator: the title by 4 s of
device time, the demo by 9 s; 16 s simulated in 12 s.

## Power

Two 18650 Li-ion cells in Keystone 1042 holders on the back, end to end along the bottom edge, in
parallel (1S2P, 3.0–4.2 V, about 5–7 Ah together). From the cells to the loads:

- **Reverse cells:** an AO3401A P-MOSFET in the plus line, its gate at the cells' minus: cells put
  in backwards leave it off and the board unpowered (it conducts both ways when they are right, so
  charging goes through it too). It cannot help one cell reversed against the other: in parallel
  they would short each other, so check both against the silkscreen's + before closing a case.
- **Protection:** DW01A + FS8205A in the pack's minus: over-charge 4.3 V, over-discharge 2.4 V,
  over-current about 3 A and short circuit, for the pack. Flat-top unprotected 18650 cells fit
  the holders.
- **USB-C input:** 5.1 kΩ on CC1 and CC2 (a sink: 5 V from any charger or computer), a 1 A
  resettable fuse, a 5 V TVS on VBUS and a USBLC6 on D+/D−.
- **Charger with power path:** a TI BQ24075 in USB500 mode (at most 500 mA from the port), 800 mA
  fast charge (RISET 1.13 kΩ), input limit by RILIM 1.18 kΩ, safety timers off (two cells in
  parallel charge longer than its longest timer; termination is by current), TS tied to 10 kΩ (no
  thermistor). Its output SYS runs the board from USB when one is plugged in and from the cells
  through its battery FET otherwise; with more load than USB gives, the cells make up the rest.
- **SYS** feeds the MT3608 backlight driver and the PAM8403 directly (no 5 V rail: both run from
  2.8–5.5 V), and a **TLV75533** (500 mA, 238 mV dropout at 500 mA, about 100 mV at this board's
  ~200 mA) for 3.3 V. It holds 3.3 V down to about 3.4 V of cell; below that the rail follows the
  cells down to 3.0 V, where the ESP32-S3 (3.0–3.6 V) still runs and the cells have under 5 % left.
  The AMS1117 it replaces needs 1.1 V of headroom: straight from the cells it would never make 3.3 V.
- **On/off:** the slide switch on the left edge drives the regulator's EN (100 kΩ holds it low
  between positions). Off, 3.3 V is gone: the module, panel logic, expander and DAC are unpowered,
  the backlight driver's EN is pulled low and the amplifier's SHDN (on 3.3 V) puts it to sleep; the
  cells still charge.

| State | Current (estimate) |
|---|---|
| ESP32-S3 + PSRAM streaming the panel | ~120 mA at 3.3 V |
| Panel logic | 25 mA at 3.3 V |
| Backlight 25.6 V × 40 mA ≈ 1.0 W | ~320 mA from 3.7 V at 85 % |
| PAM8403, moderate volume | ~100 mA |
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
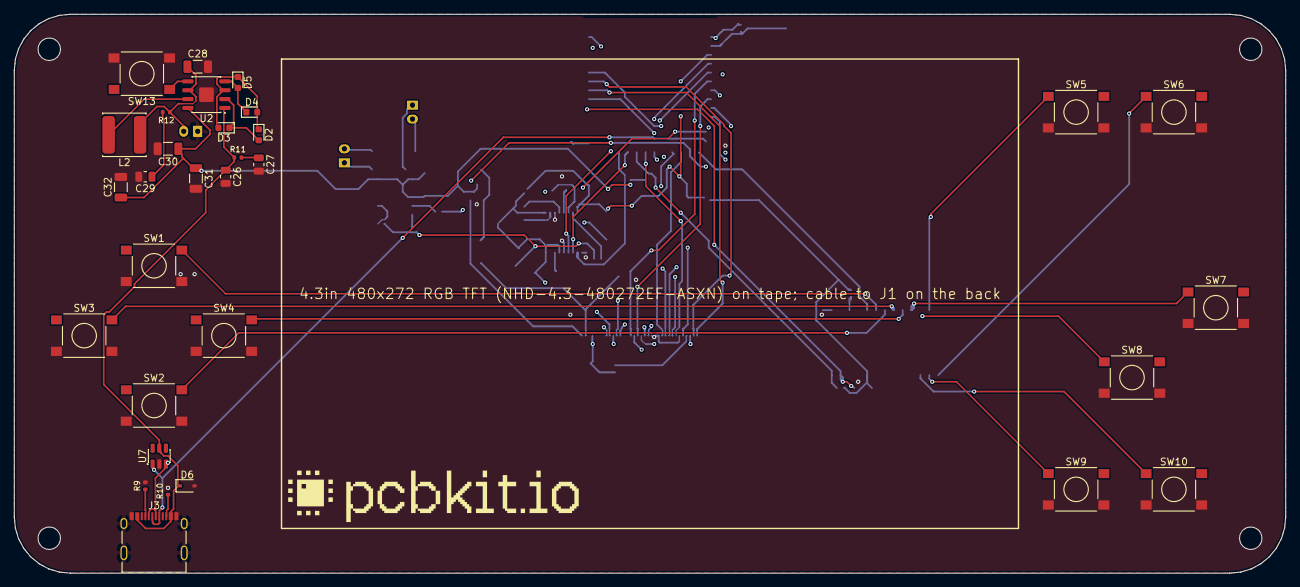
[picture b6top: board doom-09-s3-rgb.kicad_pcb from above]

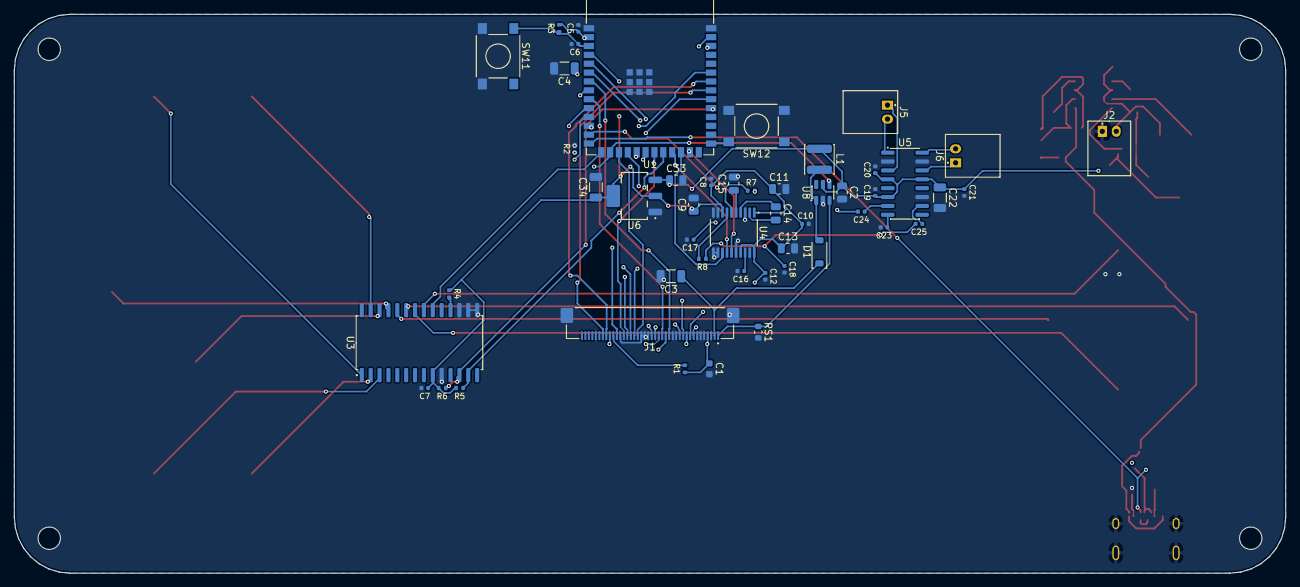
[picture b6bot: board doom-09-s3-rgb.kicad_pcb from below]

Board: 4 copper layers, 182.0 x 80.0 mm, 86 parts (50 on the bottom side), 75 nets.

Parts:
C1: 10uF; C_0603_1608Metric
C2: 22uF; C_0805_2012Metric
C3: 4.7uF; C_1206_3216Metric
C4, C22, C28, C30, C31, C32, C34: 22uF; C_1206_3216Metric
C5, C7, C8, C10, C12, C16: 100nF; C_0402_1005Metric
C6, C19, C20, C21, C23: 1uF; C_0402_1005Metric
C9, C11, C13, C26, C27, C29, C33: 10uF; C_0805_2012Metric
C14, C15: 2.2uF; C_0805_2012Metric
C17, C18: 2.2nF; C_0402_1005Metric
C24, C25: 470nF; C_0402_1005Metric
D1: schottky; D_SOD-123
D2, D3, D4, D5: blue; LED_0603_1608Metric
D6: tvs 5V; D_SOD-323
H1, H2, H3, H4: MountingHole_3.2mm_M3
J1: 54132-4062; Conn_FFC-FPC_1x40_P0.50mm_Horizontal
J2, J5, J6: S2B-PH-K-S(LF)(SN); JST_PH_S2B-PH-K_1x02_P2.00mm_Horizontal
J3: USB_C_Receptacle_USB2.0_16P
L1: 22uH; L_Power_4x4mm
L2: 1uH; L_Power_6x6mm
R1, R3, R4: 10kohm; R_0402_1005Metric
R2: 100kohm; R_0402_1005Metric
R5, R6: 4.7kohm; R_0402_1005Metric
R7, R8: 470ohm; R_0402_1005Metric
R9, R10: 5.1kohm; R_0402_1005Metric
R11, R12: 2ohm; R_0402_1005Metric
RS1: 15ohm; R_0603_1608Metric
SW1, SW2, SW3, SW4, SW5, SW6, SW7, SW8, SW9, SW10, SW11, SW12, SW13: PTS645SM43SMTR92 LFS; SW_Tactile_SPST_6x6mm_SMD
U1: ESP32-S3-WROOM-1-N16R8; ESP32-S3-WROOM-1_module_18x25.5mm_40_edge_pads_EPAD
U2: IP5306; SOIC-8-1EP_3.9x4.9mm_P1.27mm_EP2.09x2.09mm
U3: MCP23017-E/SO; SOIC-28W_7.5x17.9mm_P1.27mm
U4: PCM5102APWR; TSSOP-20_4.4x6.5mm_P0.65mm
U5: PAM8403DR; SOIC-16_3.9x9.9mm_P1.27mm
U6: AMS1117-3.3; SOT-223
U7: ESD 2-line; SOT-23-6
U8: MT3608; SOT-23-6
logo: Logo_PCBKit_pcbkit.io

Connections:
BLU3: J1.24, U1.17
BLU4: J1.25, U1.18
BLU5: J1.26, U1.19
BLU6: J1.27, U1.20
BLU7: J1.28, U1.21
BL_EN: R2.1, U1.16, U8.4
BL_SW: D1.2, L1.2, U8.1
DE: J1.34, U1.33
DISP: J1.31, R1.2
DN: J3.A7, J3.B7, U1.13, U7.3
DOWN: SW2.1, SW2.2, U3.22
DP: J3.A6, J3.B6, U1.14, U7.1
EN: C6.1, R3.1, SW11.1, SW11.2, U1.3
ENTER: SW10.1, SW10.2, U3.3
FIRE: SW7.1, SW7.2, U3.25
GAUGE1: D2.2, D3.1, U2.2
GAUGE2: D2.1, D3.2, D4.2, D5.1, U2.3
GAUGE3: D4.1, D5.2, U2.4
GND: C1.2, C2.2, C3.2, C4.2, C5.2, C6.2, C7.2, C8.2, C9.2, C10.2, C11.2, C12.2, C13.2, C15.2, C16.2, C17.2, C18.2, C19.2, C20.2, C21.2, C22.2, C23.2, C26.2, C27.2, C28.2, C29.2, C30.2, C31.2, C32.2, C33.2, C34.2, D6.2, J1.3, J1.5, J1.6, J1.7, J1.13, J1.14, J1.21, J1.22, J1.23, J1.29, J1.36, J1.MP, J2.1, J3.A1, J3.B1, J3.S1, R2.2, R9.2, R10.2, RS1.2, SW1.3, SW1.4, SW2.3, SW2.4, SW3.3, SW3.4, SW4.3, SW4.4, SW5.3, SW5.4, SW6.3, SW6.4, SW7.3, SW7.4, SW8.3, SW8.4, SW9.3, SW9.4, SW10.3, SW10.4, SW11.3, SW11.4, SW12.3, SW12.4, SW13.3, SW13.4, U1.1, U1.40, U1.41, U2.9, U3.10, U3.15, U3.16, U3.17, U4.3, U4.9, U4.10, U4.11, U4.12, U4.16, U4.19, U5.2, U5.11, U5.15, U6.1, U7.2, U8.2
GRN2: J1.15, U1.7
GRN3: J1.16, U1.8
GRN4: J1.17, U1.9
GRN5: J1.18, U1.10
GRN6: J1.19, U1.11
GRN7: J1.20, U1.12
HSYNC: J1.32, U1.32
I2S_BCK: U1.24, U4.13
I2S_DIN: U1.23, U4.14
I2S_LRCK: U1.25, U4.15
KEYS_INT: U1.15, U3.20
LED_A: C3.1, D1.1, J1.2
LED_K: J1.1, RS1.1, U8.3
LEFT: SW3.1, SW3.2, U3.23
LINE_L: C17.1, C24.2, R7.2
LINE_R: C18.1, C25.2, R8.1
MENU: SW9.1, SW9.2, U3.2
unnamed: C14.2, U4.2
unnamed: C14.1, U4.4
unnamed: C15.1, U4.5
unnamed: C16.1, U4.18
unnamed: C23.1, U5.8
unnamed: C24.1, U5.7
unnamed: C25.1, U5.10
unnamed: L2.2, U2.7
unnamed: R4.2, U3.18
unnamed: R7.1, U4.6
unnamed: R8.2, U4.7
unnamed: SW12.1, SW12.2, U1.27
unnamed: SW13.1, SW13.2, U2.5
PCLK: J1.30, U1.35
RED3: J1.8, U1.39
RED4: J1.9, U1.38
RED5: J1.10, U1.4
RED6: J1.11, U1.5
RED7: J1.12, U1.6
RIGHT: SW4.1, SW4.2, U3.24
SCL: R6.1, U1.31, U3.12
SDA: R5.1, U1.22, U3.13
SPK_LN: J5.1, U5.3
SPK_LP: J5.2, U5.1
SPK_RN: J6.1, U5.14
SPK_RP: J6.2, U5.16
STRAFE_L: SW5.1, SW5.2, U3.27
STRAFE_R: SW6.1, SW6.2, U3.1
U2Support/C6_P: C27.1, R11.2
U2Support/C7_P: C29.1, R12.2
UP: SW1.1, SW1.2, U3.21
USE: SW8.1, SW8.2, U3.26
V3: C1.1, C4.1, C5.1, C7.1, C8.1, C9.1, C10.1, C11.1, C12.1, C13.1, C34.1, J1.4, R1.1, R3.2, R4.1, R5.2, R6.2, U1.2, U3.9, U4.1, U4.8, U4.17, U4.20, U6.2, U6.4
V5: C2.1, C19.1, C20.1, C21.1, C22.1, C30.1, C31.1, C32.1, C33.1, L1.1, U2.8, U5.4, U5.6, U5.13, U6.3, U8.5
VBAT: C28.1, J2.2, L2.1, R12.1, U2.6
VBUS: C26.1, D6.1, J3.A4, J3.B4, R11.1, U2.1, U7.5
VSYNC: J1.33, U1.34
usb/power/cc1: J3.A5, R9.1
usb/power/cc2: J3.B5, R10.1
